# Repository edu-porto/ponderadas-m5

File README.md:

# ponderadas-m5
 Repo com todas atividades ponderadas do modúlo 5

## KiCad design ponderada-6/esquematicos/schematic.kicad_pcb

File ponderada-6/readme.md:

# Atividade Ponderada 6

## Objetivo

O objetivo desta atividade é montar uma placa com o Raspberry Pi Pico e criar um esquemático.

## Atividades Desenvolvidas

Nesta atividade, foram realizados três itens:

1. Esquemático da PCB, conforme visualizado na imagem abaixo:

2. Layout da PCB:

3. Pasta Gerber que contém os arquivos necessários para que empresas possam fabricar o circuito desenvolvido. Na imagem a seguir, há uma representação da placa:

## Estrutura de Pastas

Os arquivos do repositório estão organizados da seguinte forma:

```
├── assets
│   ├── imagens desenvolvidas
├── esquematicos
│   ├── gerber
│   │   ├── arquivos para impressão da placa em gerber
│   ├── esquemáticos do circuito e pcb desenvolvidos com o KiCad
```

## Sobre o circuito 

Este circuito foi inspirado no protótipo desenvolvido com o Raspberry Pi Pico e um relé.

[Circuito em funcionamento](https://youtu.be/Uo2QEAf8ozU)

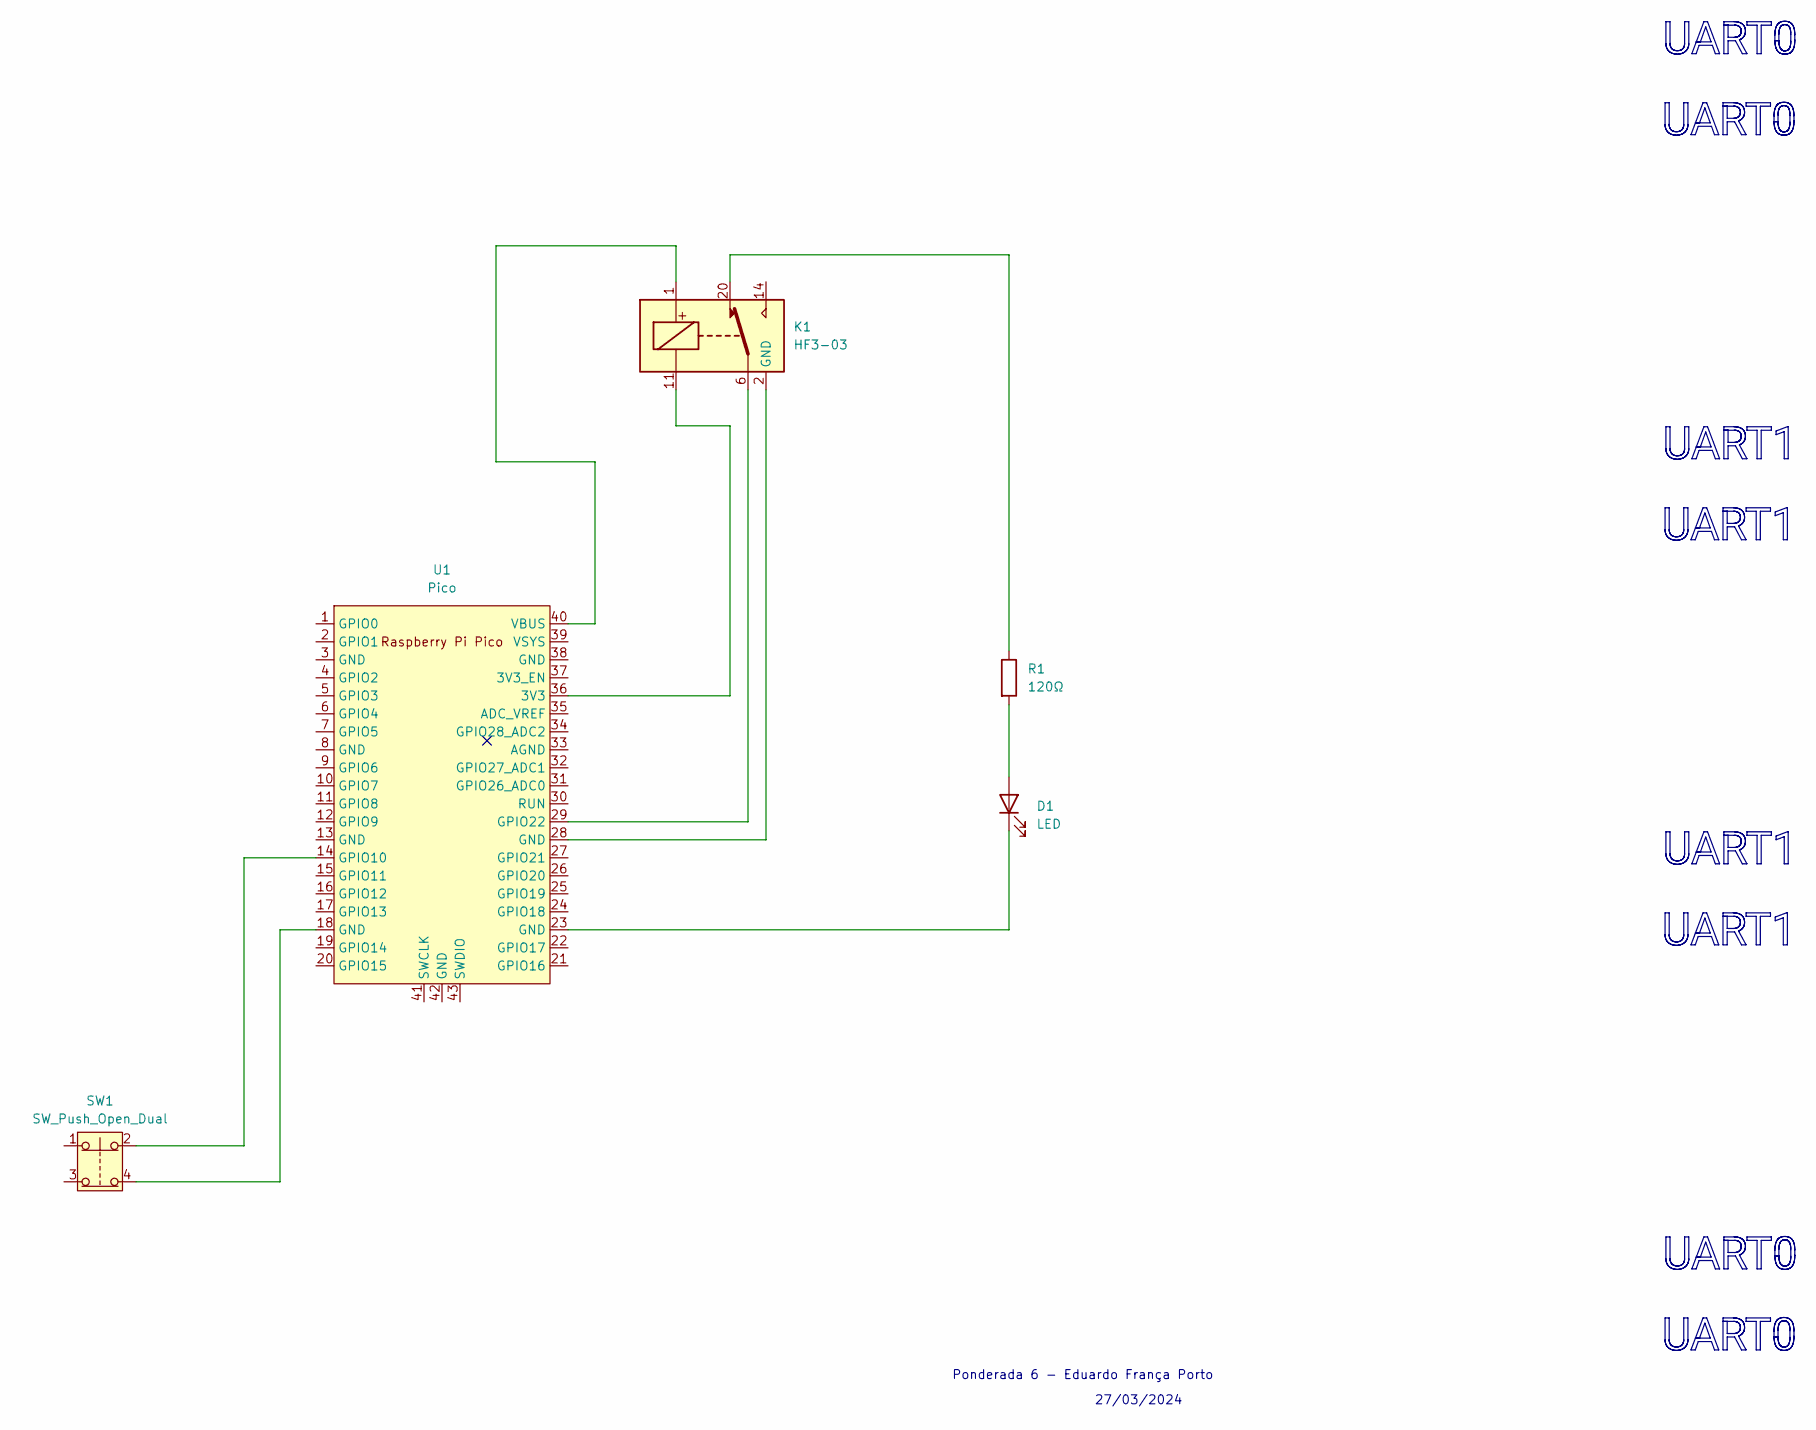
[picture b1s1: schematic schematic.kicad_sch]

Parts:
D1: LED; LED_D3.0mm_Horizontal_O1.27mm_Z2.0mm
K1: HF3-03; Relay_SPDT_AXICOM_HF3Series_75ohms_Pitch1.27mm
R1: 120Ω; R_0201_0603Metric
SW1: SW_Push_Open_Dual; Push_E-Switch_KS01Q01
U1: Pico; RPi_Pico_SMD_TH

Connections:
unnamed: D1.2 (A), R1.2
unnamed: D1.1 (K), U1.23 (GND)
unnamed: K1.2 (GND), K1.5 (GND), K1.7 (GND), K1.10 (GND), K1.12 (GND), K1.13 (GND), K1.15 (GND), K1.17 (GND), K1.19 (GND), K1.21 (GND), K1.22 (GND), U1.28 (GND)
unnamed: K1.20, R1.1
unnamed: SW1.4, U1.18 (GND)
unnamed: K1.11, U1.36 (3V3)
unnamed: SW1.2, U1.14 (GPIO10)
unnamed: K1.6, U1.29 (GPIO22)
unnamed: K1.1, U1.40 (VBUS)

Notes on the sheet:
Ponderada 6 - Eduardo França Porto
27/03/2024

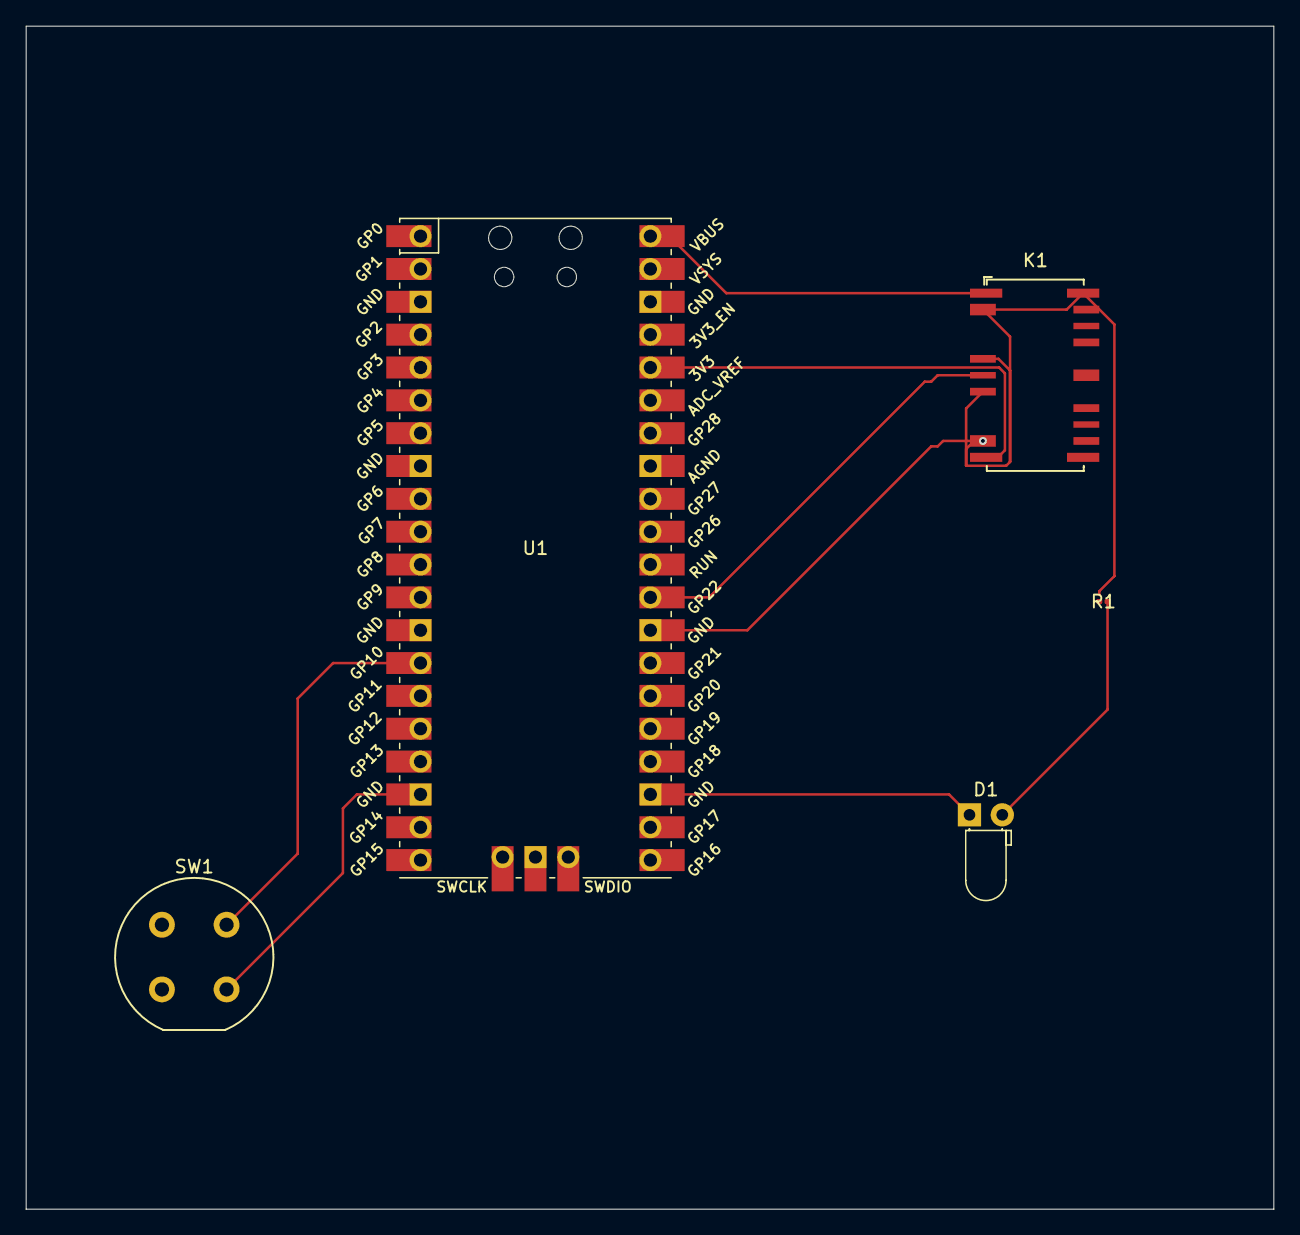
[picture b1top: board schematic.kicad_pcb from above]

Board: 2 copper layers, 96.5 x 91.5 mm, 5 parts (0 on the bottom side), 9 nets.

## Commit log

2024-02-28 feat Código bem encaminhado
2024-03-01 atividade pronta
2024-03-31 ponderada 6
2024-04-02 feat : crud done
    HTMX SUCKSSSS
2024-04-02 fix : fixing api route
2024-04-02 feat : begin to make robot api
2024-04-03 FEAT : Robot connection done
2024-04-03 update : more logs
2024-04-03 FEAT : assignment done ✅✅✅
2024-04-05 FEAT :+1: Prova feita
2024-04-05 Revert "FEAT :+1: Prova feita"
    This reverts commit a1f0f298e7bdecd7ffbbaf87e93e5cc735a21979.
